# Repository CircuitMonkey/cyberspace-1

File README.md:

# cyberspace-1
Card Edge Slot-based 8-bit experimental computer with a Cyberpunk aesthetic.

## Why?
I wanted to make a 8-bit card-edge style computer.  8-bit computers were the first thing I learned to design in school back in the 80's.  Our mid-level education courses involved engineering students wire-wrapping and then programming their own Z80 computer system, with the next semester involving the addition and more programming of peripherals.  So I want to get back to that headspace for a bit.  I see many other hobbyists doing this with Z80, 6502 and even RP2040 chips.  This not sure yet what processor I will choose but it will be something with a good emulator environment on the Mac or Linux.

## About the name...
I want to create a system that has a Cyberpunk aesthetic and in the book Neuromancer, there is a Cyberspace "Deck" called the Cyberspace7 by Ono-Sendai and that implies the existence of Cyberspace 1 through 6.  So for my own amusement I've decided to call this experiment the Cyberspace 1 along with creating logos for Cyberspace product as well as a logo for Ono-Sendai Company.

&nbsp;&nbsp;&nbsp;&nbsp;

&nbsp;&nbsp;&nbsp;&nbsp;

## License
I've decided to make this project with the MIT license.  Do whatever you want with it.

## Release Notes
### 2023 Early November
Created GitHub repository.

### 2023 Mid November
Roughed out basic design for all main boards.  Backplane, 6502, Memory, Clock, Video card.  Placement seems to be satisfactory.

### 2024 January
Bring up of Backplane and Clock board largely succesful!
 * Backplane. No issues found so far.
 * Clock board crystal circuit has error (used Schmidt buffer (HCT14) instead of regular buffer (HCT04). Will fix in later revision.

## To Do
Sound Card, Keyboard and game controller input card.

Each of these peripheral cards are likely to be RP2040 chips masquerading as
custom devices like the Video card will be.  I wish to use USB keyboards and
USB game (perhaps bluetooth?) controllers, so I will look at making a card with multiple USB jacks on it.  The card would handle HID and Storage devices.

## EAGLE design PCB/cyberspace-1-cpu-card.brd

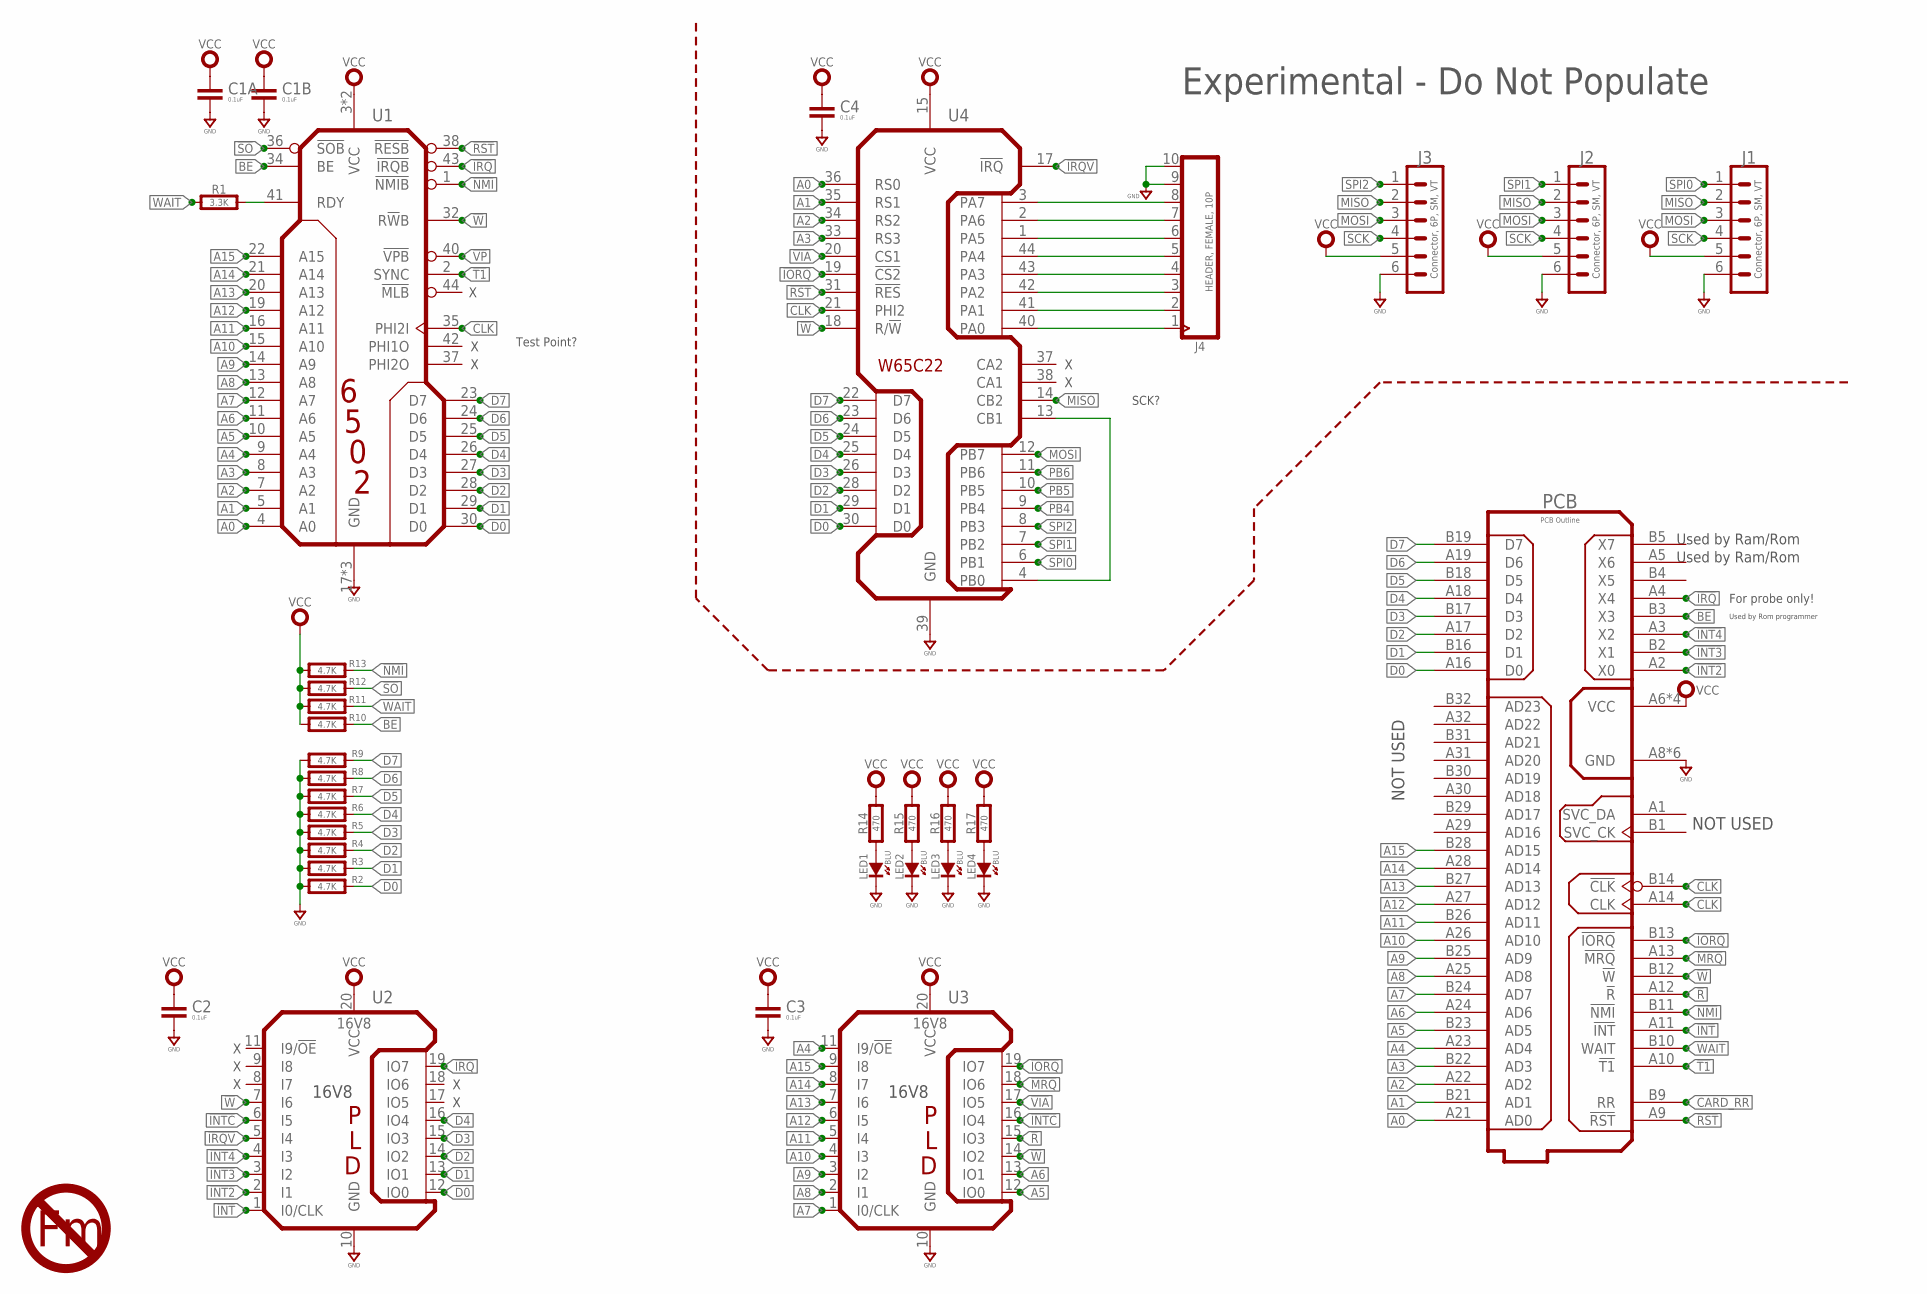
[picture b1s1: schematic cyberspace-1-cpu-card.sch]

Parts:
C1A, C1B, C2, C3, C4: 0.1uF; 0603-CAP
J1, J2, J3: Connector, 6P, SM, VT; BM06B-SRSS-TB
J4: HEADER, FEMALE, 10P; H10-2.54
LED1, LED2, LED3, LED4: BLU; SMD_0603
PCB: PCB Outline; CYBERSPACE-CARD-TYPE-1A
R1: 3.3K; 0603-RES
R2, R3, R4, R5, R6, R7, R8, R9, R10, R11, R12, R13: 4.7K; 0603-RES
R14, R15, R16, R17: 470; 0603-RES
U1: 6502 Processor; TQFP-44-10
U2, U3: 16V8; SOP20
U4: W65C22; TQFP-44-10
U$2: NO-FERMIUM-5MM

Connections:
!CLK: PCB.B14 (!CLK)
!INT: PCB.A11 (!INT), U2.1 (I0/CLK)
!INT2: PCB.A2 (X0), U2.2 (I1)
!INT3: PCB.B2 (X1), U2.3 (I2)
!INT4: PCB.A3 (X2), U2.4 (I3)
!INTC: U2.6 (I5), U3.16 (IO4)
!IORQ: PCB.B13 (!IORQ), U3.19 (IO7), U4.19 (!CS2)
!IRQ: PCB.A4 (X4), U1.43 (!IRQB), U2.19 (IO7)
!IRQV: U2.5 (I4), U4.17 (!IRQ)
!MRQ: PCB.A13 (!MRQ), U3.18 (IO6)
!NMI: PCB.B11 (!NMI), R13.2, U1.1 (!NMIB)
!R: PCB.A12 (!R), U3.15 (IO3)
!RST: PCB.A9 (!RST), U1.38 (!RESB), U4.31 (!RES)
!SO: R12.2, U1.36 (!SOB)
!T1: PCB.A10 (!T1), U1.2 (SYNC)
!VIA: U3.17 (IO5), U4.20 (CS1)
!VP: U1.40 (!VPB)
!W: PCB.B12 (!W), U1.32 (R!W!B), U2.7 (I6), U3.14 (IO2), U4.18 (R/!W)
A0: PCB.A21 (AD0), U1.4 (A0), U4.36 (RS0)
A1: PCB.B21 (AD1), U1.5 (A1), U4.35 (RS1)
A2: PCB.A22 (AD2), U1.7 (A2), U4.34 (RS2)
A3: PCB.B22 (AD3), U1.8 (A3), U4.33 (RS3)
A4: PCB.A23 (AD4), U1.9 (A4), U3.11 (I9/!OE)
A5: PCB.B23 (AD5), U1.10 (A5), U3.12 (IO0)
A6: PCB.A24 (AD6), U1.11 (A6), U3.13 (IO1)
A7: PCB.B24 (AD7), U1.12 (A7), U3.1 (I0/CLK)
A8: PCB.A25 (AD8), U1.13 (A8), U3.2 (I1)
A9: PCB.B25 (AD9), U1.14 (A9), U3.3 (I2)
A10: PCB.A26 (AD10), U1.15 (A10), U3.4 (I3)
A11: PCB.B26 (AD11), U1.16 (A11), U3.5 (I4)
A12: PCB.A27 (AD12), U1.19 (A12), U3.6 (I5)
A13: PCB.B27 (AD13), U1.20 (A13), U3.7 (I6)
A14: PCB.A28 (AD14), U1.21 (A14), U3.8 (I7)
A15: PCB.B28 (AD15), U1.22 (A15), U3.9 (I8)
BE: PCB.B3 (X3), R10.2, U1.34 (BE)
CARD_RR: PCB.B9 (RR)
CLK: PCB.A14 (CLK), U1.35 (PHI2I), U4.21 (PHI2)
D0: PCB.A16 (D0), R2.2, U1.30 (D0), U2.12 (IO0), U4.30 (D0)
D1: PCB.B16 (D1), R3.2, U1.29 (D1), U2.13 (IO1), U4.29 (D1)
D2: PCB.A17 (D2), R4.2, U1.28 (D2), U2.14 (IO2), U4.28 (D2)
D3: PCB.B17 (D3), R5.2, U1.27 (D3), U2.15 (IO3), U4.26 (D3)
D4: PCB.A18 (D4), R6.2, U1.26 (D4), U2.16 (IO4), U4.25 (D4)
D5: PCB.B18 (D5), R7.2, U1.25 (D5), U4.24 (D5)
D6: PCB.A19 (D6), R8.2, U1.24 (D6), U4.23 (D6)
D7: PCB.B19 (D7), R9.2, U1.23 (D7), U4.22 (D7)
GND: C1A.2, C1B.2, C2.2, C3.2, C4.2, J1.6, J2.6, J3.6, J4.9, J4.10, LED1.K (C), LED2.K (C), LED3.K (C), LED4.K (C), PCB.A8 (GND), PCB.A15 (GND), PCB.A20 (GND), PCB.B8 (GND), PCB.B15 (GND), PCB.B20 (GND), R2.1, R3.1, R4.1, R5.1, R6.1, R7.1, R8.1, R9.1, U1.17 (GND), U1.18 (GND), U1.39 (GND), U2.10 (GND), U3.10 (GND), U4.39 (GND)
MISO: J1.2, J2.2, J3.2, U4.14 (CB2)
MOSI: J1.3, J2.3, J3.3, U4.12 (PB7)
unnamed: J4.1, U4.40 (PA0)
unnamed: J4.2, U4.41 (PA1)
unnamed: J4.3, U4.42 (PA2)
unnamed: J4.4, U4.43 (PA3)
unnamed: J4.5, U4.44 (PA4)
unnamed: J4.6, U4.1 (PA5)
unnamed: J4.7, U4.2 (PA6)
unnamed: J4.8, U4.3 (PA7)
unnamed: U4.4 (PB0), U4.13 (CB1)
unnamed: R1.2, U1.41 (RDY)
unnamed: LED1.A, R14.1
unnamed: LED2.A, R15.1
unnamed: LED3.A, R16.1
unnamed: LED4.A, R17.1
PB4: U4.9 (PB4)
PB5: U4.10 (PB5)
PB6: U4.11 (PB6)
SCK: J1.4, J2.4, J3.4
SPI0: J1.1, U4.6 (PB1)
SPI1: J2.1, U4.7 (PB2)
SPI2: J3.1, U4.8 (PB3)
VCC: C1A.1, C1B.1, C2.1, C3.1, C4.1, J1.5, J2.5, J3.5, PCB.A6 (VCC), PCB.A7 (VCC), PCB.B6 (VCC), PCB.B7 (VCC), R10.1, R11.1, R12.1, R13.1, R14.2, R15.2, R16.2, R17.2, U1.3 (VCC), U1.31 (VCC), U2.20 (VCC), U3.20 (VCC), U4.15 (VCC)
WAIT: PCB.B10 (WAIT), R1.1, R11.2

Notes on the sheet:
Experimental - Do Not Populate
NOT USED
Used by Ram/Rom
X X X
X X
SCK?
Test Point?
For probe only!
Used by Rom programmer

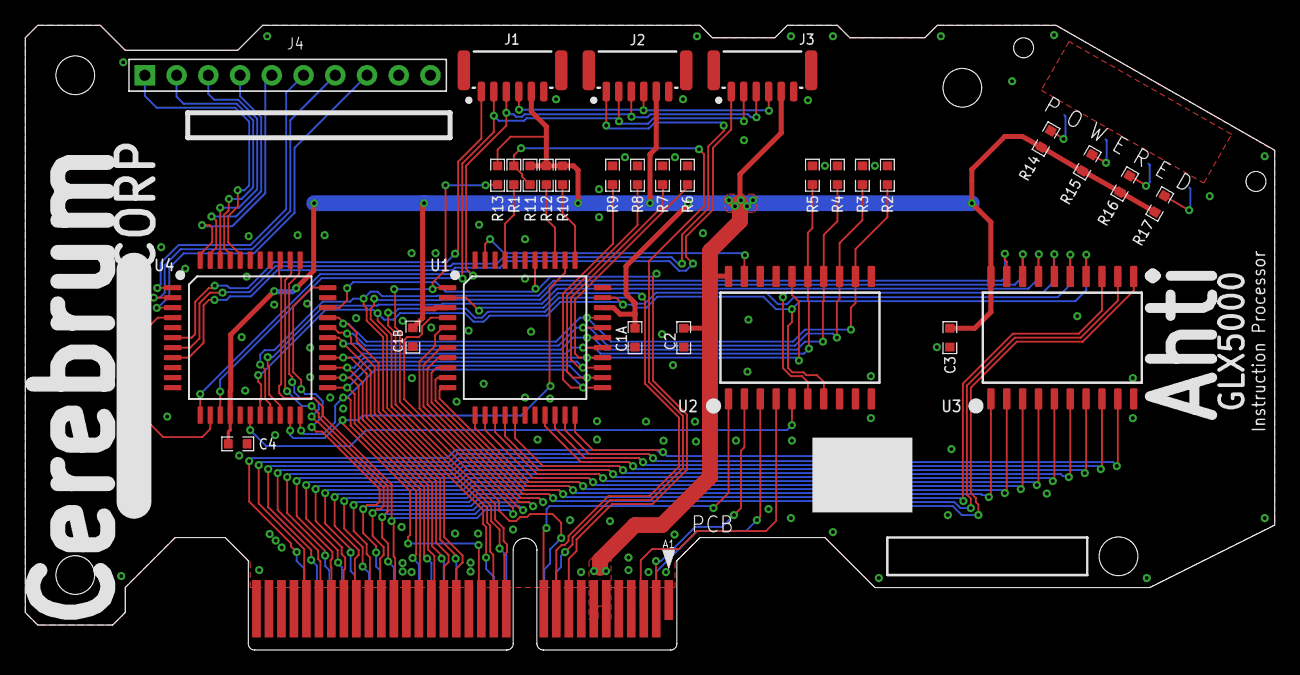
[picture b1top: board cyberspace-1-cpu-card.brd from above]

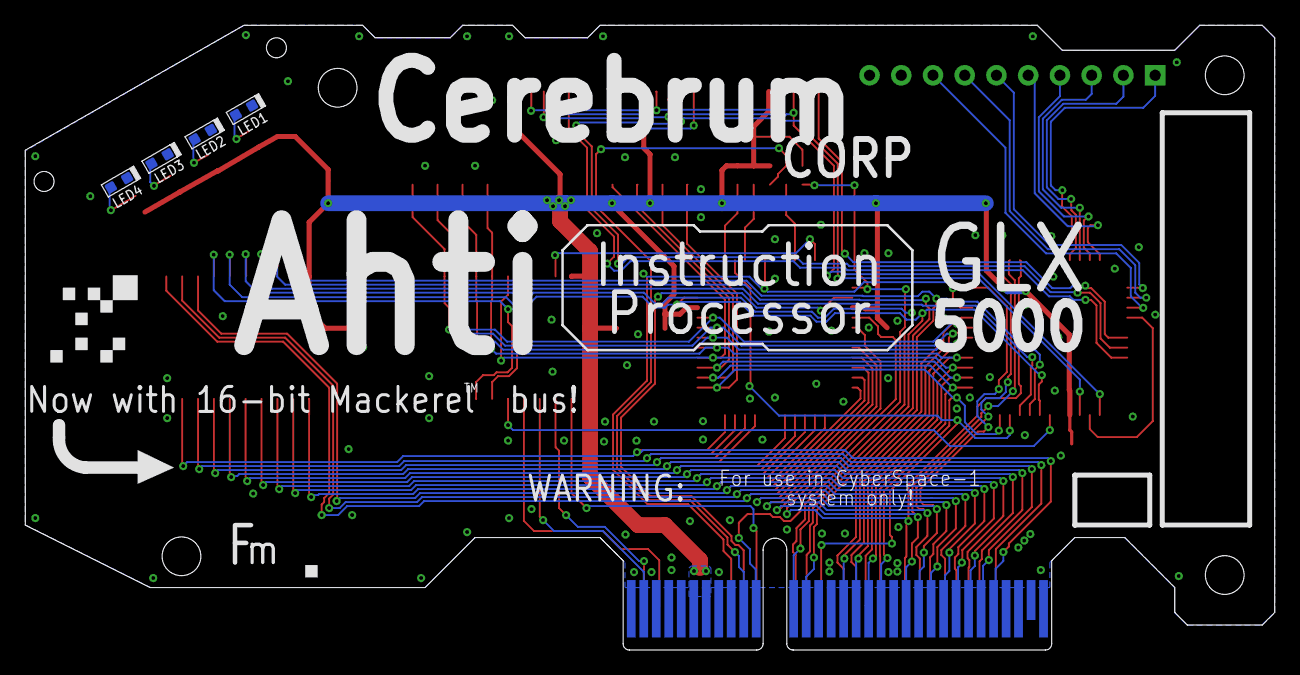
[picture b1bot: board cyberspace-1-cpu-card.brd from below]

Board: 2 copper layers, 100.0 x 50.0 mm, 36 parts (5 on the bottom side), 65 nets.

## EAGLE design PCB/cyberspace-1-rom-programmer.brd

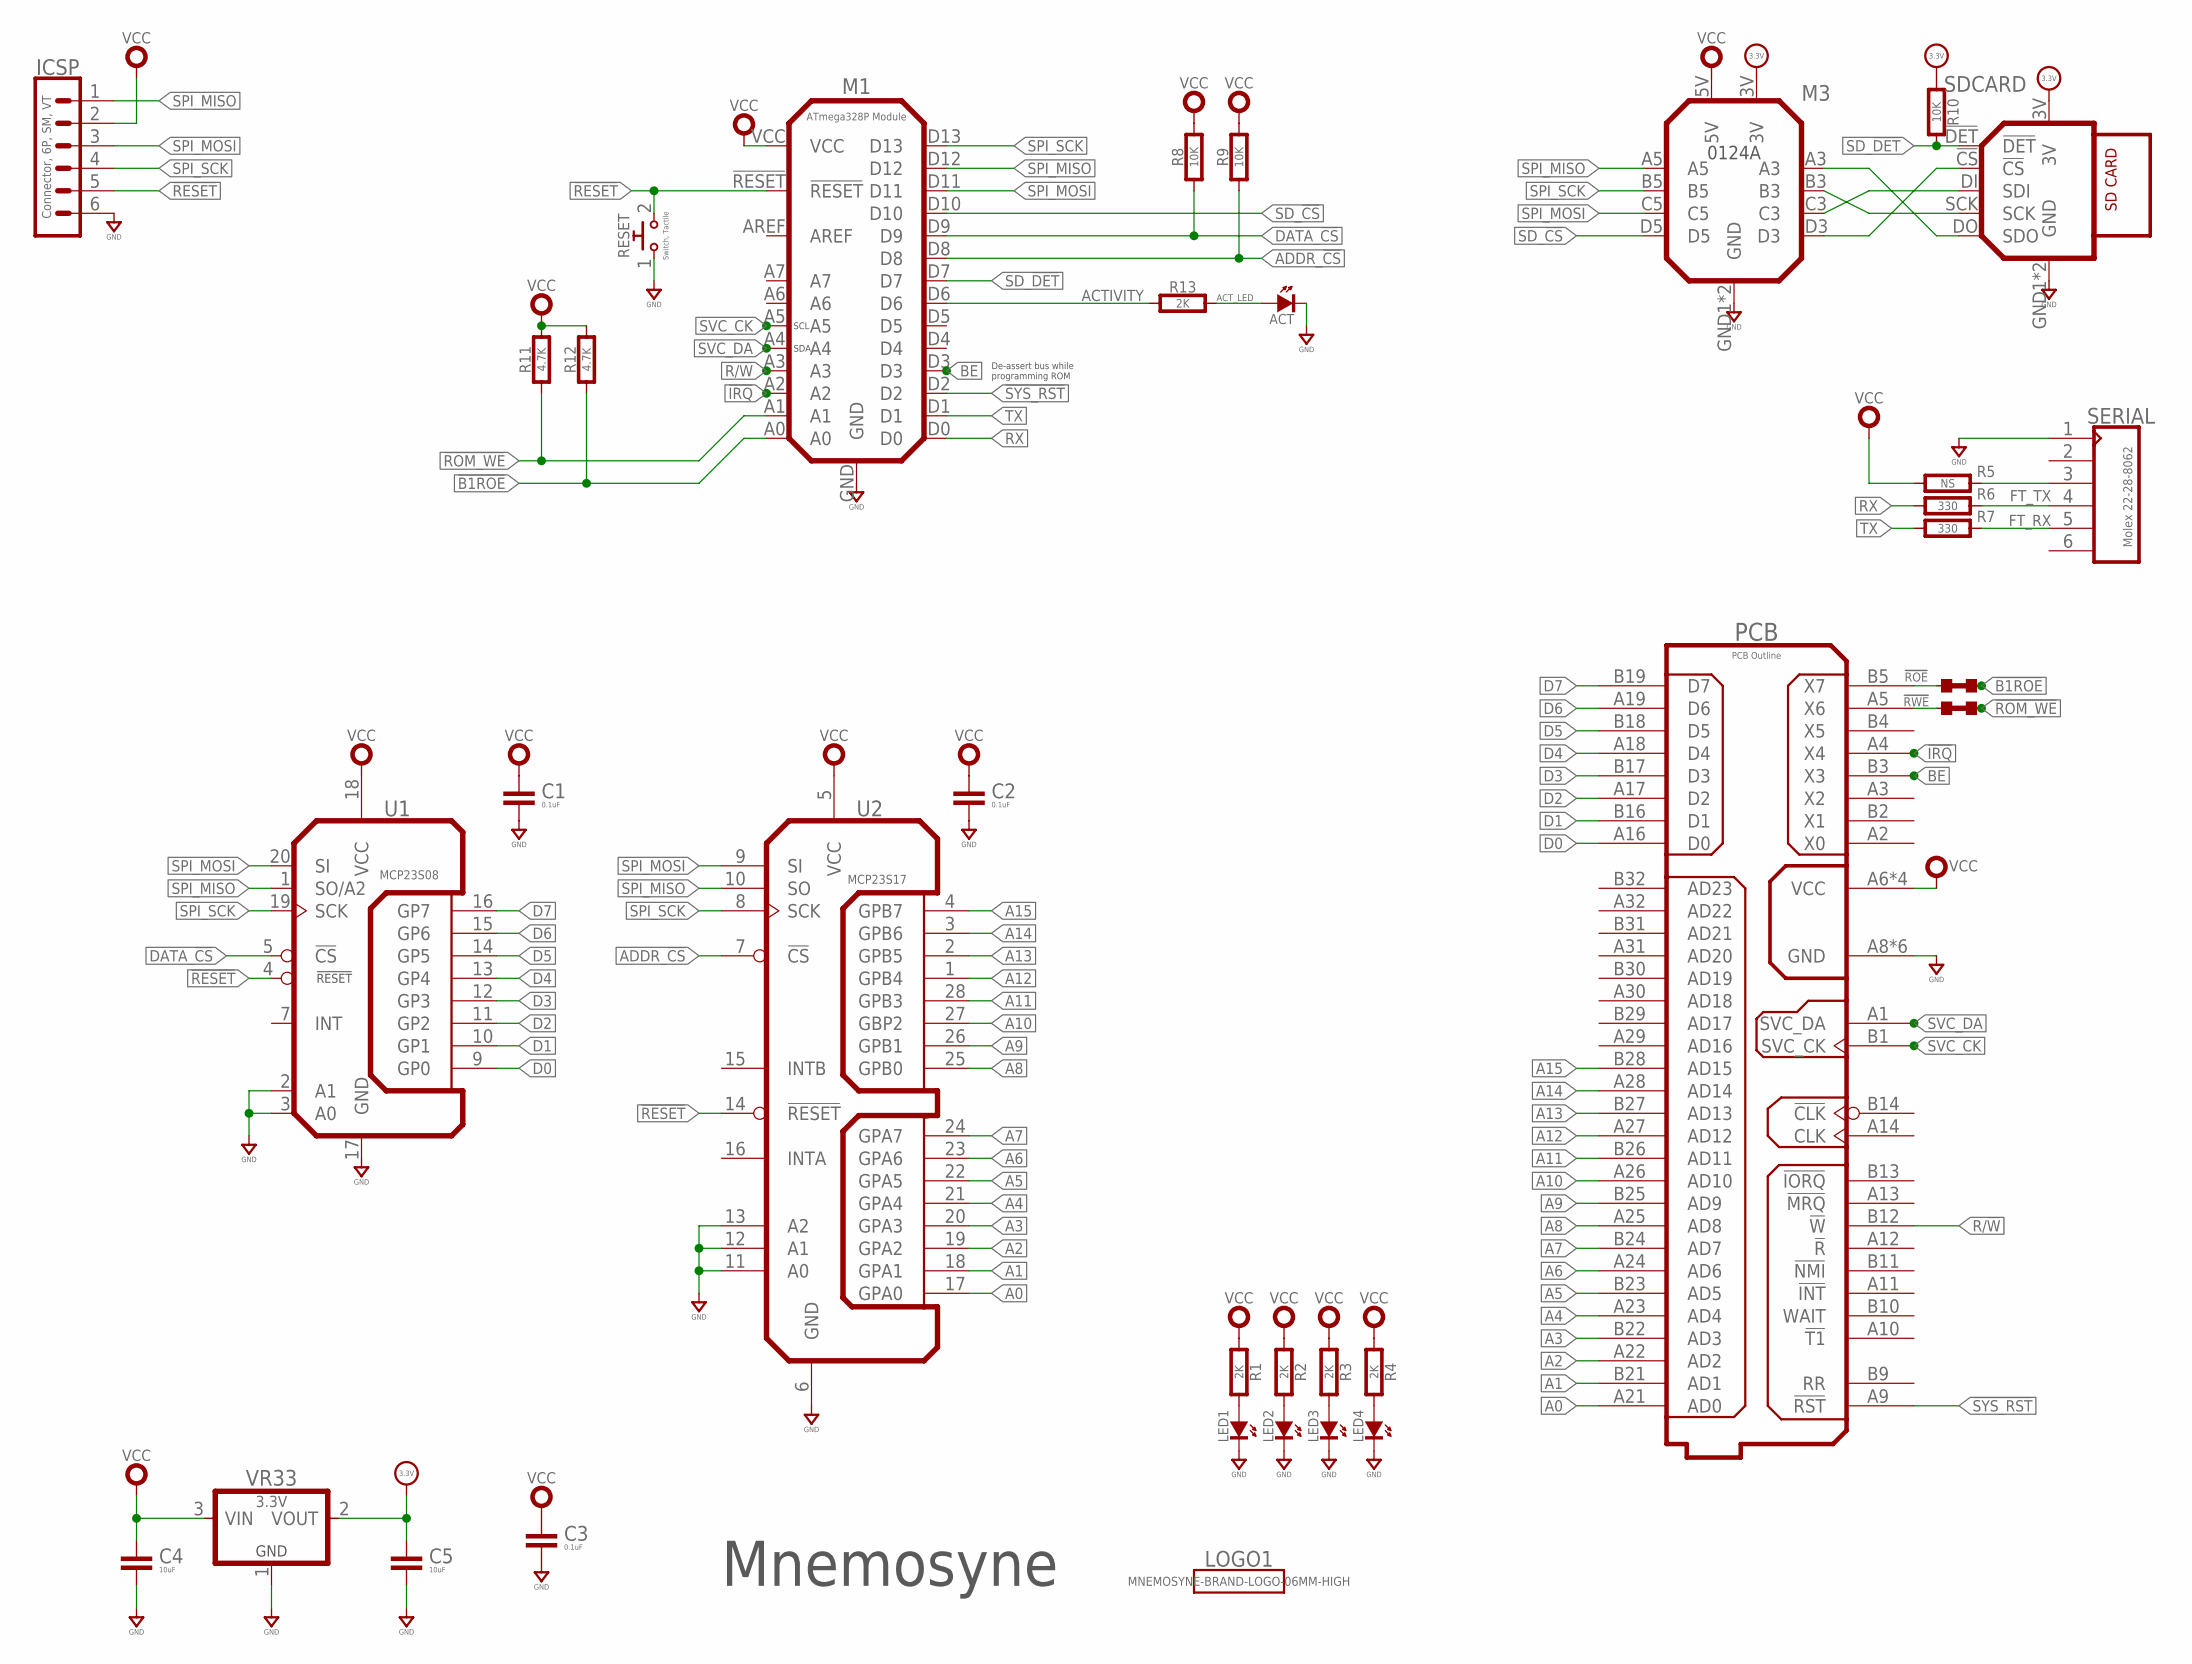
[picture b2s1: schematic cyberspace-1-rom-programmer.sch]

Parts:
!ROE: NP; 0603-SHORT
!RWE: NP; 0603-SHORT
ACT: SMT0603; SMD_0603
C1, C2, C3: 0.1uF; 0603-CAP
C4, C5: 10uF; 0603-CAP
ICSP: Connector, 6P, SM, VT; BM06B-SRSS-TB
LED1, LED2, LED3, LED4: SMT0603; SMD_0603
LOGO1: MNEMOSYNE-BRAND-LOGO-06MM-HIGH; MNEMOSYNE-06MM
M1: ATmega328P Module; 0119A
M3: 0124A
PCB: PCB Outline; CYBERSPACE-CARD-TYPE-1A
R1, R2, R3, R4, R13: 2K; 0603-RES
R5: NS; 0603-RES
R6, R7: 330; 0603-RES
R8, R9, R10: 10K; 0603-RES
R11, R12: 4.7K; 0603-RES
RESET: Switch, Tactile; TC-0202
SDCARD: 0127REV-A; 0127A
SERIAL: Molex 22-28-8062; MA06X1-RA-THD
U1: MCP23S08; QFN-20
U2: MCP23S17; QFN-28-6X6
VR33: 3.3V; SOT-23

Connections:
!B1ROE: !ROE.4 (2), M1.A0, R12.1
!IRQ: M1.A2, PCB.A4 (X4)
!RESET: ICSP.5, M1.!RESET, RESET.2, U1.4 (!RESET), U2.14 (!RESET)
!ROM_WE: !RWE.4 (2), M1.A1, R11.1
!SYS_RST: M1.D2, PCB.A9 (!RST)
+3.3V: C5.1, M3.3V, R10.2, SDCARD.3V, VR33.2 (VOUT)
A0: PCB.A21 (AD0), U2.17 (GPA0)
A1: PCB.B21 (AD1), U2.18 (GPA1)
A2: PCB.A22 (AD2), U2.19 (GPA2)
A3: PCB.B22 (AD3), U2.20 (GPA3)
A4: PCB.A23 (AD4), U2.21 (GPA4)
A5: PCB.B23 (AD5), U2.22 (GPA5)
A6: PCB.A24 (AD6), U2.23 (GPA6)
A7: PCB.B24 (AD7), U2.24 (GPA7)
A8: PCB.A25 (AD8), U2.25 (GPB0)
A9: PCB.B25 (AD9), U2.26 (GPB1)
A10: PCB.A26 (AD10), U2.27 (GBP2)
A11: PCB.B26 (AD11), U2.28 (GPB3)
A12: PCB.A27 (AD12), U2.1 (GPB4)
A13: PCB.B27 (AD13), U2.2 (GPB5)
A14: PCB.A28 (AD14), U2.3 (GPB6)
A15: PCB.B28 (AD15), U2.4 (GPB7)
ACTIVITY: M1.D6, R13.1
ACT_LED: ACT.A, R13.2
ADDR_!CS: M1.D8, R9.1, U2.7 (!CS)
BE: M1.D3, PCB.B3 (X3)
D0: PCB.A16 (D0), U1.9 (GP0)
D1: PCB.B16 (D1), U1.10 (GP1)
D2: PCB.A17 (D2), U1.11 (GP2)
D3: PCB.B17 (D3), U1.12 (GP3)
D4: PCB.A18 (D4), U1.13 (GP4)
D5: PCB.B18 (D5), U1.14 (GP5)
D6: PCB.A19 (D6), U1.15 (GP6)
D7: PCB.B19 (D7), U1.16 (GP7)
DATA_!CS: M1.D9, R8.1, U1.5 (!CS)
FT_RX: R7.1, SERIAL.5
FT_TX: R6.1, SERIAL.4
GND: ACT.K (C), C1.2, C2.2, C3.2, C4.2, C5.2, ICSP.6, LED1.K (C), LED2.K (C), LED3.K (C), LED4.K (C), M1.GND, M3.GND1 (GND), M3.GND2 (GND), PCB.A8 (GND), PCB.A15 (GND), PCB.A20 (GND), PCB.B8 (GND), PCB.B15 (GND), PCB.B20 (GND), RESET.1, SDCARD.GND1 (GND), SDCARD.GND2 (GND), SERIAL.1, U1.2 (A1), U1.3 (A0), U1.17 (GND), U2.6 (GND), U2.11 (A0), U2.12 (A1), U2.13 (A2), VR33.1 (GND)
unnamed: M3.A3, SDCARD.DO (SDO)
unnamed: M3.B3, SDCARD.SCK
unnamed: M3.C3, SDCARD.DI (SDI)
unnamed: R5.1, SERIAL.3
unnamed: M3.D3, SDCARD.!CS
unnamed: LED1.A, R1.2
unnamed: LED2.A, R2.2
unnamed: LED3.A, R3.2
unnamed: !ROE.3 (1), PCB.B5 (X7)
unnamed: !RWE.3 (1), PCB.A5 (X6)
unnamed: LED4.A, R4.2
R/!W: M1.A3, PCB.B12 (!W)
RX: M1.D0, R6.2
SD_!CS: M1.D10, M3.D5
SD_!DET: M1.D7, R10.1, SDCARD.!DET
SPI_MISO: ICSP.1, M1.D12, M3.A5, U1.1 (SO/A2), U2.10 (SO)
SPI_MOSI: ICSP.3, M1.D11, M3.C5, U1.20 (SI), U2.9 (SI)
SPI_SCK: ICSP.4, M1.D13, M3.B5, U1.19 (SCK), U2.8 (SCK)
SVC_CK: M1.A5, PCB.B1 (SVC_CK)
SVC_DA: M1.A4, PCB.A1 (SVC_DA)
TX: M1.D1, R7.2
VCC: C1.1, C2.1, C3.1, C4.1, ICSP.2, M1.VCC, M3.5V, PCB.A6 (VCC), PCB.A7 (VCC), PCB.B6 (VCC), PCB.B7 (VCC), R1.1, R2.1, R3.1, R4.1, R5.2, R8.2, R9.2, R11.2, R12.2, U1.18 (VCC), U2.5 (VCC), VR33.3 (VIN)

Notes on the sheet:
SDA
SCL
Mnemosyne
De-assert bus while programming ROM

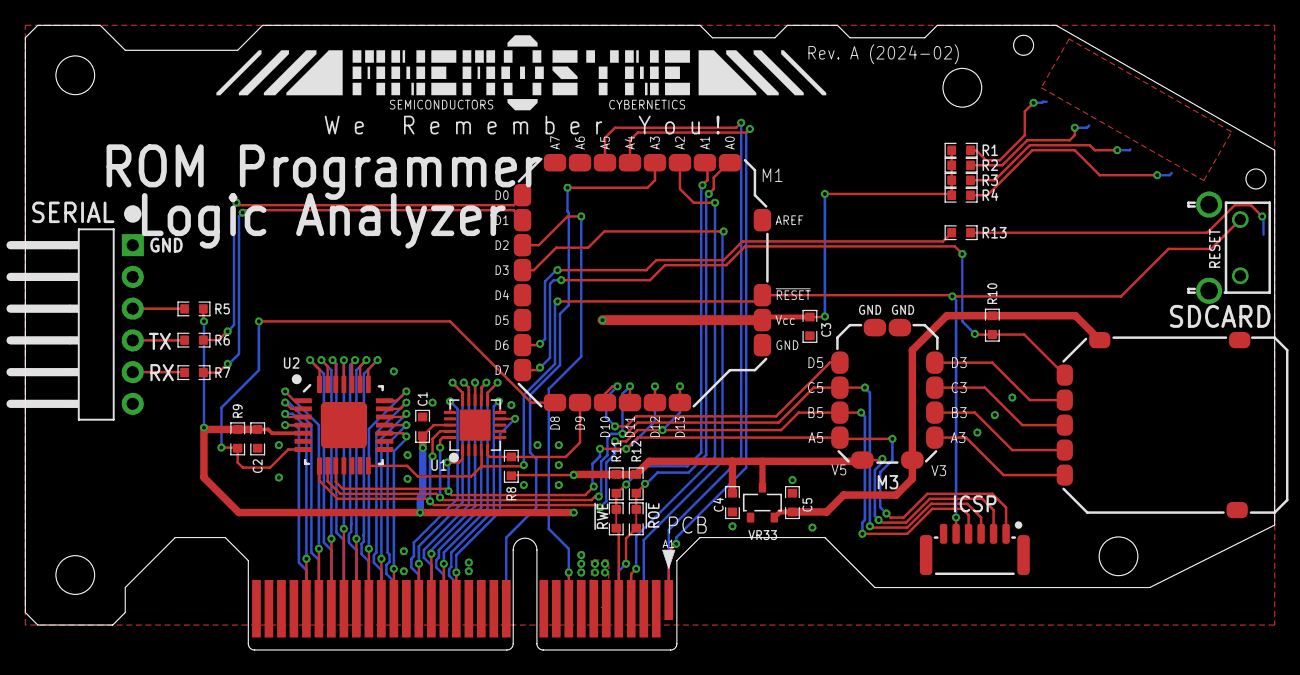
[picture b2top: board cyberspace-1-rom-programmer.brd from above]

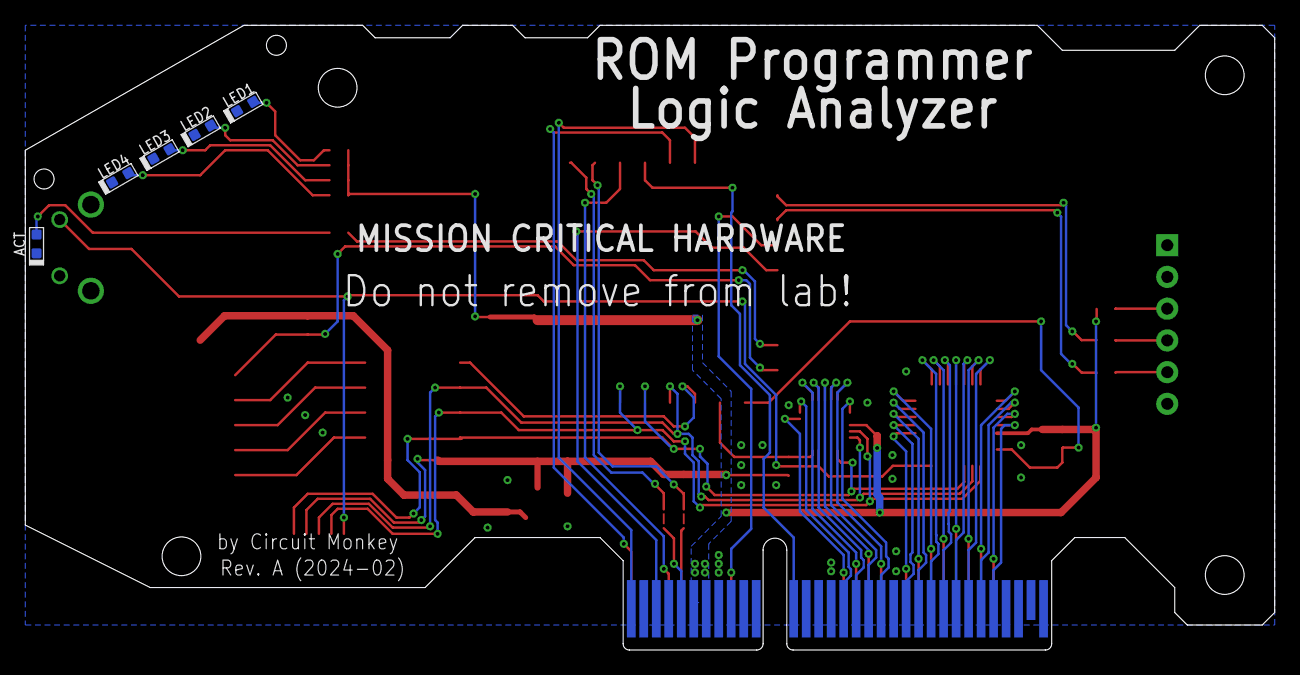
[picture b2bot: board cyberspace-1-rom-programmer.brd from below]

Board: 2 copper layers, 100.0 x 50.0 mm, 36 parts (5 on the bottom side), 60 nets.

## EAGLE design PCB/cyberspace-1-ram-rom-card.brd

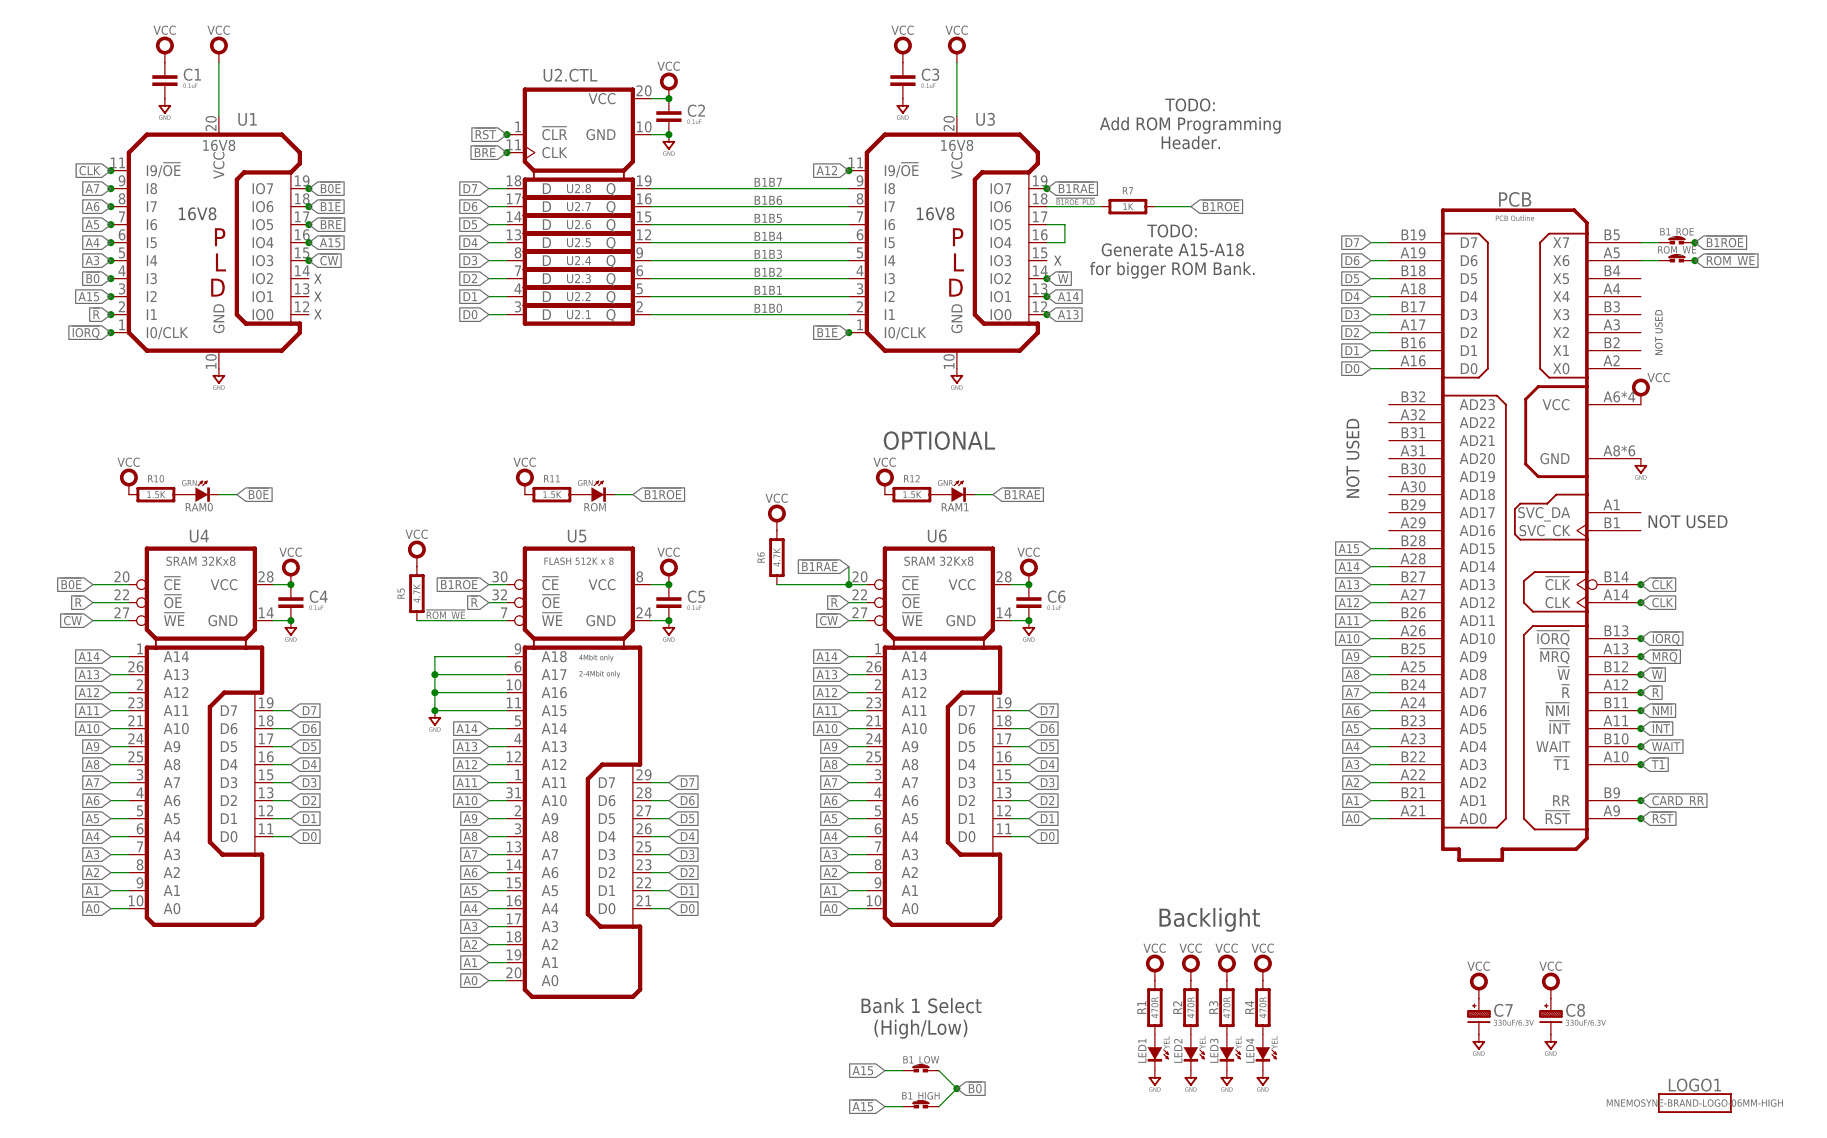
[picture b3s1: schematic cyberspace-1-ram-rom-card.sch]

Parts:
B1_HIGH, B1_LOW, B1_ROE: SOLDER_JUMPER-60MIL-RND; SOLDER_JUMP_60MIL_RND
C1, C2, C3, C4, C5, C6: 0.1uF; 0603-CAP
C7, C8: 330uF/6.3V; CAP_ALUM_SMT_6.3
LED1, LED2, LED3, LED4: YEL; SMD_0603
LOGO1: MNEMOSYNE-BRAND-LOGO-06MM-HIGH; MNEMOSYNE-06MM
PCB: PCB Outline; CYBERSPACE-CARD-TYPE-1A
R1, R2, R3, R4: 470R; 0603-RES
R5, R6: 4.7K; 0603-RES
R7: 1K; 0603-RES
R10, R11, R12: 1.5K; 0603-RES
RAM0: GRN; SMD_0603
RAM1: GNR; SMD_0603
ROM: GRN; SMD_0603
ROM_WE: SOLDER_JUMPER-60MIL-RND; SOLDER_JUMP_60MIL_RND
U1, U3: 16V8; SOP20
U2: 74AHCT273NS; SO20
U4, U6: SRAM 32Kx8; SOP28-330W
U5: FLASH 512K x 8; TSOP32-14X8MM

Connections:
!A15: B1_HIGH.1, U1.16 (IO4)
!B0: B1_HIGH.2, B1_LOW.2, U1.4 (I3)
!B0E: RAM0.K (C), U1.19 (IO7), U4.20 (!CE)
!B1E: U1.18 (IO6), U3.1 (I0/CLK)
!B1RAE: R6.1, RAM1.K (C), U3.19 (IO7), U6.20 (!CE)
!B1ROE: B1_ROE.2, R7.2, ROM.K (C), U5.30 (!CE)
!B1ROE_PLD: R7.1, U3.18 (IO6)
!BRE: U1.17 (IO5), U2.11 (CLK)
!CLK: PCB.B14 (!CLK)
!CW: U1.15 (IO3), U4.27 (!WE), U6.27 (!WE)
!INT: PCB.A11 (!INT)
!IORQ: PCB.B13 (!IORQ), U1.1 (I0/CLK)
!MRQ: PCB.A13 (!MRQ)
!NMI: PCB.B11 (!NMI)
!R: PCB.A12 (!R), U1.2 (I1), U4.22 (!OE), U5.32 (!OE), U6.22 (!OE)
!ROM_WE: R5.1, ROM_WE.2, U5.7 (!WE)
!RST: PCB.A9 (!RST), U2.1 (!CLR)
!T1: PCB.A10 (!T1)
!W: PCB.B12 (!W), U3.14 (IO2)
A0: PCB.A21 (AD0), U4.10 (A0), U5.20 (A0), U6.10 (A0)
A1: PCB.B21 (AD1), U4.9 (A1), U5.19 (A1), U6.9 (A1)
A2: PCB.A22 (AD2), U4.8 (A2), U5.18 (A2), U6.8 (A2)
A3: PCB.B22 (AD3), U1.5 (I4), U4.7 (A3), U5.17 (A3), U6.7 (A3)
A4: PCB.A23 (AD4), U1.6 (I5), U4.6 (A4), U5.16 (A4), U6.6 (A4)
A5: PCB.B23 (AD5), U1.7 (I6), U4.5 (A5), U5.15 (A5), U6.5 (A5)
A6: PCB.A24 (AD6), U1.8 (I7), U4.4 (A6), U5.14 (A6), U6.4 (A6)
A7: PCB.B24 (AD7), U1.9 (I8), U4.3 (A7), U5.13 (A7), U6.3 (A7)
A8: PCB.A25 (AD8), U4.25 (A8), U5.3 (A8), U6.25 (A8)
A9: PCB.B25 (AD9), U4.24 (A9), U5.2 (A9), U6.24 (A9)
A10: PCB.A26 (AD10), U4.21 (A10), U5.31 (A10), U6.21 (A10)
A11: PCB.B26 (AD11), U4.23 (A11), U5.1 (A11), U6.23 (A11)
A12: PCB.A27 (AD12), U3.11 (I9/!OE), U4.2 (A12), U5.12 (A12), U6.2 (A12)
A13: PCB.B27 (AD13), U3.12 (IO0), U4.26 (A13), U5.4 (A13), U6.26 (A13)
A14: PCB.A28 (AD14), U3.13 (IO1), U4.1 (A14), U5.5 (A14), U6.1 (A14)
A15: B1_LOW.1, PCB.B28 (AD15), U1.3 (I2)
B1B0: U2.2 (Q), U3.2 (I1)
B1B1: U2.5 (Q), U3.3 (I2)
B1B2: U2.6 (Q), U3.4 (I3)
B1B3: U2.9 (Q), U3.5 (I4)
B1B4: U2.12 (Q), U3.6 (I5)
B1B5: U2.15 (Q), U3.7 (I6)
B1B6: U2.16 (Q), U3.8 (I7)
B1B7: U2.19 (Q), U3.9 (I8)
CARD_RR: PCB.B9 (RR)
CLK: PCB.A14 (CLK), U1.11 (I9/!OE)
D0: PCB.A16 (D0), U2.3 (D), U4.11 (D0), U5.21 (D0), U6.11 (D0)
D1: PCB.B16 (D1), U2.4 (D), U4.12 (D1), U5.22 (D1), U6.12 (D1)
D2: PCB.A17 (D2), U2.7 (D), U4.13 (D2), U5.23 (D2), U6.13 (D2)
D3: PCB.B17 (D3), U2.8 (D), U4.15 (D3), U5.25 (D3), U6.15 (D3)
D4: PCB.A18 (D4), U2.13 (D), U4.16 (D4), U5.26 (D4), U6.16 (D4)
D5: PCB.B18 (D5), U2.14 (D), U4.17 (D5), U5.27 (D5), U6.17 (D5)
D6: PCB.A19 (D6), U2.17 (D), U4.18 (D6), U5.28 (D6), U6.18 (D6)
D7: PCB.B19 (D7), U2.18 (D), U4.19 (D7), U5.29 (D7), U6.19 (D7)
GND: C1.2, C2.2, C3.2, C4.2, C5.2, C6.2, C7.- (N), C8.- (N), LED1.K (C), LED2.K (C), LED3.K (C), LED4.K (C), PCB.A8 (GND), PCB.A15 (GND), PCB.A20 (GND), PCB.B8 (GND), PCB.B15 (GND), PCB.B20 (GND), U1.10 (GND), U2.10 (GND), U3.10 (GND), U4.14 (GND), U5.6 (A17), U5.9 (A18), U5.10 (A16), U5.11 (A15), U5.24 (GND), U6.14 (GND)
unnamed: U3.16 (IO4), U3.17 (IO5)
unnamed: LED1.A, R1.1
unnamed: LED2.A, R2.1
unnamed: R10.2, RAM0.A
unnamed: LED3.A, R3.1
unnamed: LED4.A, R4.1
unnamed: R11.2, ROM.A
unnamed: R12.2, RAM1.A
unnamed: B1_ROE.1, PCB.B5 (X7)
unnamed: PCB.A5 (X6), ROM_WE.1
VCC: C1.1, C2.1, C3.1, C4.1, C5.1, C6.1, C7.+, C8.+, PCB.A6 (VCC), PCB.A7 (VCC), PCB.B6 (VCC), PCB.B7 (VCC), R1.2, R2.2, R3.2, R4.2, R5.2, R6.2, R10.1, R11.1, R12.1, U1.20 (VCC), U2.20 (VCC), U3.20 (VCC), U4.28 (VCC), U5.8 (VCC), U6.28 (VCC)
WAIT: PCB.B10 (WAIT)

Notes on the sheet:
NOT USED
X X X
OPTIONAL
TODO: Generate A15-A18 for bigger ROM Bank.
TODO: Add ROM Programming Header.
Backlight
Bank 1 Select (High/Low)

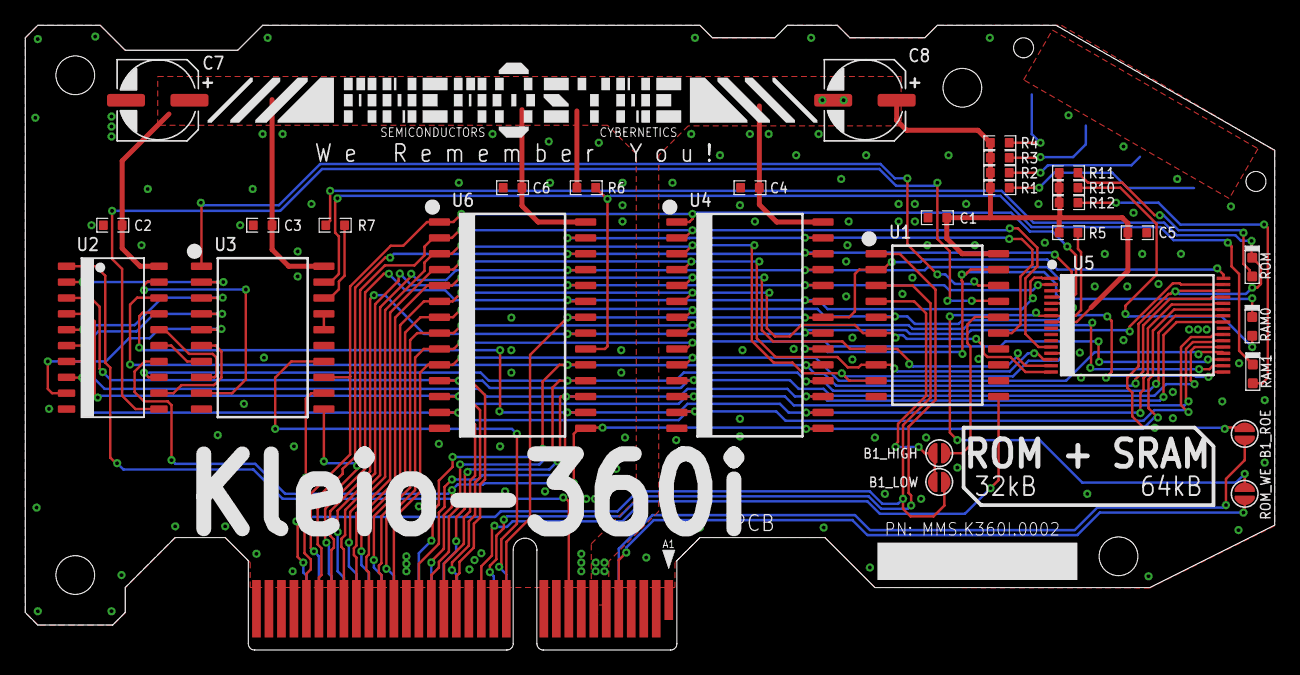
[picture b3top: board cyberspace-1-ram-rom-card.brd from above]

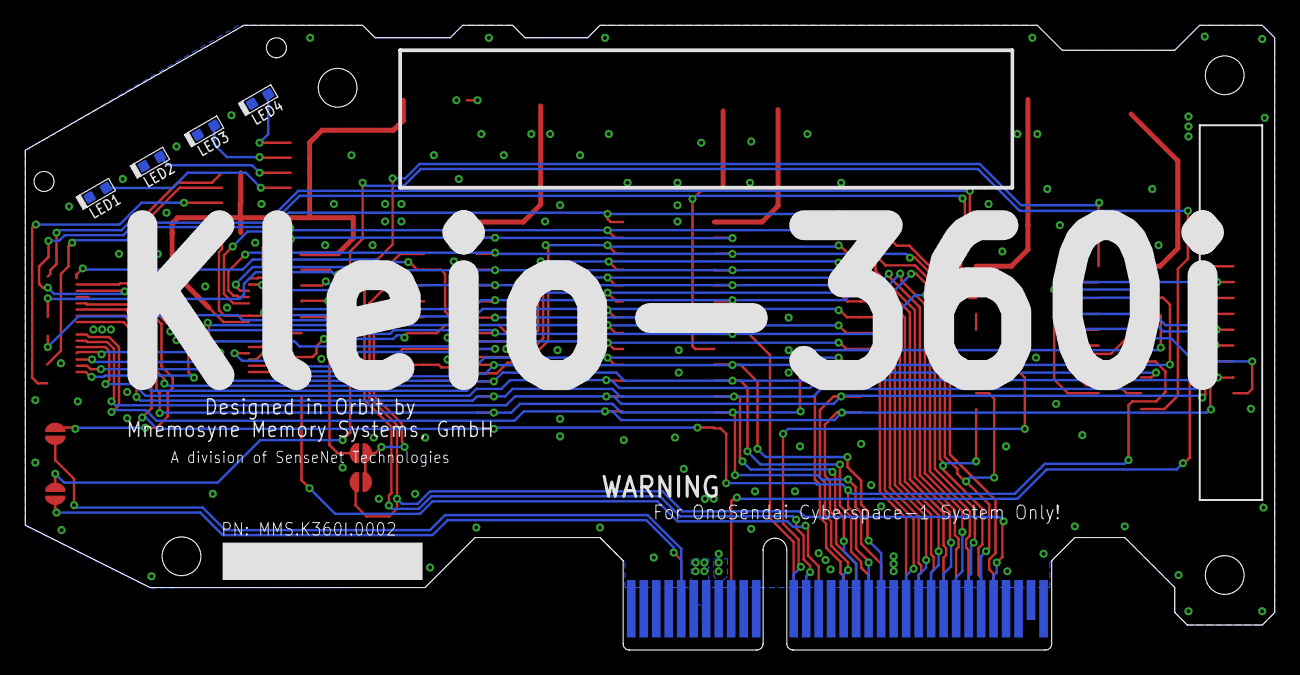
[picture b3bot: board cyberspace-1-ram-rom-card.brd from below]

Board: 2 copper layers, 100.0 x 50.0 mm, 37 parts (4 on the bottom side), 59 nets.
